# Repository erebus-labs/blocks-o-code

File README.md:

blocks-o-code
=============

#A Block of Code
+ *Title:* Physical manipulators for developing and implementing short programing routines 
+ *Project Short Name:* A Block of Code (ABC)
+ *Sponsors:* 
  + [Dr. Mike Borowczak](https://www.linkedin.com/in/mborowczak) @ [Erebus Labs](http://www.erebuslabs.com)
  + [Dr. Andrea Burrows] (http://uwyo.academia.edu/AndreaBurrows) @ [University of Wyoming] (http://www.uwyo.edu/seced/faculty-staff/andrea-burrows.html)
+ *Senior Design Team:* 
  + Jacob Mickiewicz 
  + Tyler Hart
  + Daniel Frister
  + Greg Stromire
  + Nathan Bryant
+ *PSU Academic Advisor:* [Roy Kravitz](http://www.pdx.edu/directory/name/roy_kravitz) 
+ *Targeted Users:* Infants to High School aged children, parents and their educators

##About A Block of Code

Blocks of Code are connectable “blocks” that mimic a simple-grammar programming language. 

The fundamental grammar contain 4 types of blocks:
+ Value Blocks
  + numbers (ints/doubles) – stringing these blocks together forms longer numbers [0,1,2,3,4,5]; [6,7,8,9,.]
  + variables
+ Operator Blocks
  + simple binary operators (*,/,-,+,%?): 
  + equivalence operators (<,>,==, !=,<=,>=)
+ Control Blocks (start and end)
  + if structures
  + while structures
  + explicit encapsulation ( )
+ Output Blocks

##Background

Algorithms, logical constructs and the foundations of programming are generally limited to computer-based instances. No physical manipulators exist that expose children to programming as they do for number and alphabet systems, mechanics, art, etc.  Build a prototype for building blocks that can be attached through internal magnets, these magnets perform two actions 
1. physical connection and 
2. logical circuit connections.

##Current Feature List
- [x] Open Source Hardware Design & Board (can use “closed source” components: ASICs, uC, etc.)
- [x] Must Have a Multi-Chip solution – e.g. no single SoC;
- [x] Fundamental grammar functioning; assignment; binary operators; 
- [x] Open Software Repository (github)
- [x] Multi-function blocks – e.g. 6 (or 4) binary operators on a single block; depending on connections/which side “faces up” operation changes 
- [x] Separate “power” blocks

##Wish List
- [ ] Hardware cost <$3 per unit (average cost for a set 20 = $60)
- [ ] Unexposed Connectors (e.g. Magnetic  + Inductive coupling between blocks?)
- [ ] Power: Ultra Low power operation
- [ ] Power
  - [ ] Built in power source / power pack
  - [ ] Built in power source w/inductance recharge
- [ ] Computer GUI/Phone App:
  - [ ] simulate a set of blocks (pre build) 
  - [ ] take a picture of a set of blocks and execute code (they don't even have to be REAL blocks - could be paper!)

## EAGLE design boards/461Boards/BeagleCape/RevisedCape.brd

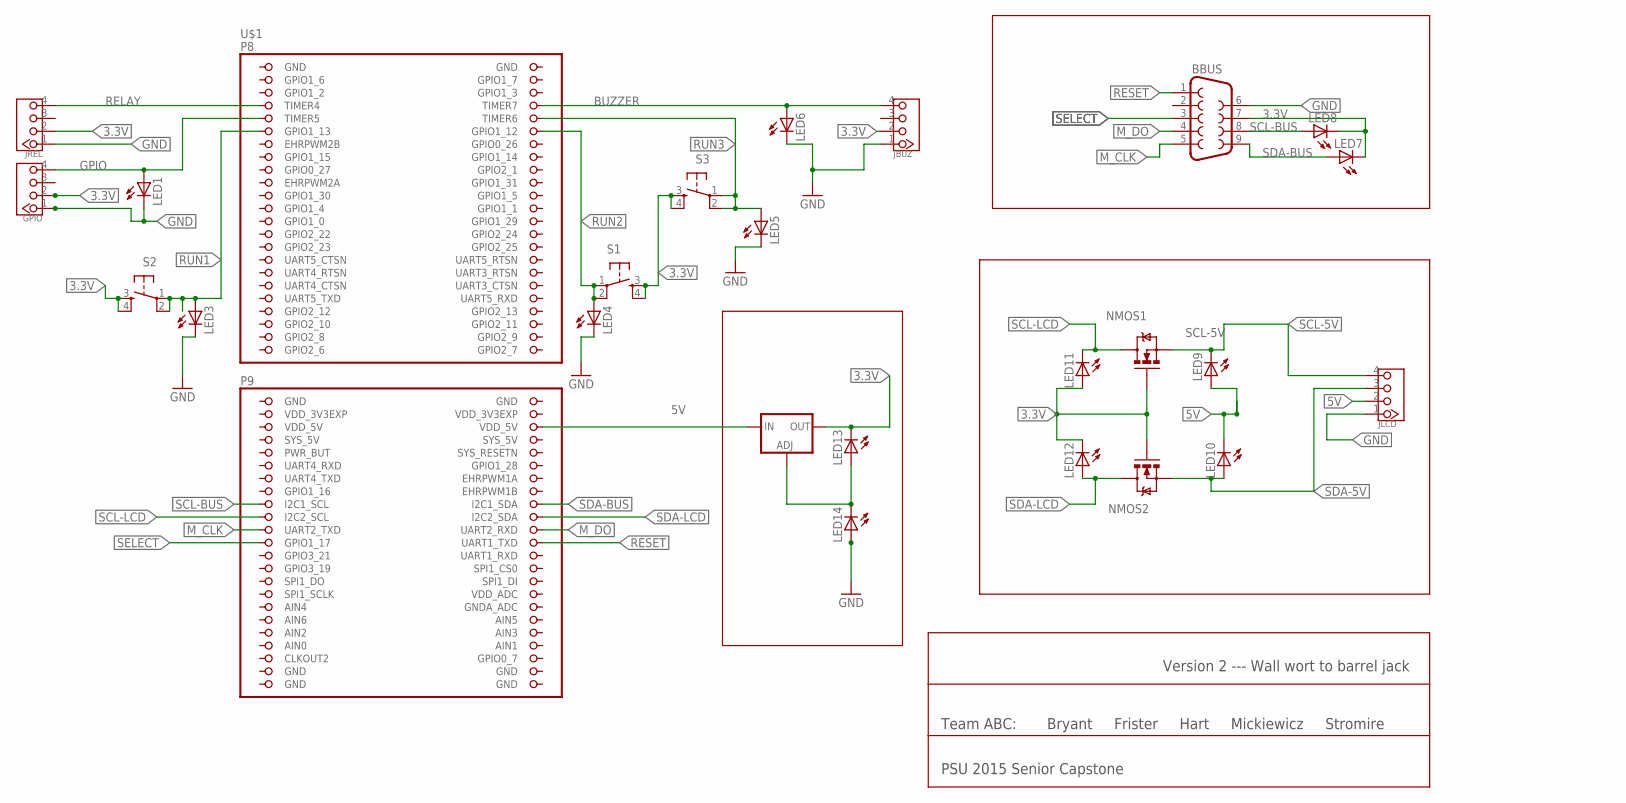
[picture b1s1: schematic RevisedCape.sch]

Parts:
3.3VREG: V_REG_317SINK; TO220-ADJ
BBUS: F09H
GPIO: TWIG-4P-2.0-2.0; 4P-2.0
JBUZ: TWIG-4P-2.0-2.0; 4P-2.0
JLCD: TWIG-4P-2.0-2.0; 4P-2.0
JREL: TWIG-4P-2.0-2.0; 4P-2.0
LED1, LED3, LED4, LED5, LED6, LED7, LED8, LED9, LED10, LED11, LED12, LED13, LED14: LED3MM
NMOS1, NMOS2: MOSFET-NCHANNEL2N7000; TO-92
S1, S2, S3: TAC_SWITCHPTH; TACTILE-PTH
U$1: BEAGLEBONE_OUTLINE; BEAGLEBONE_SHIELD

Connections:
3.3V: 3.3VREG.OUT, BBUS.7, GPIO.2, JBUZ.2, JREL.2, LED7.K (C), LED8.K (C), LED11.A, LED12.K (C), LED13.K (C), NMOS1.2 (G), NMOS2.2 (G), S1.3, S1.4, S2.3, S2.4, S3.3, S3.4
5V: 3.3VREG.IN, JLCD.2, LED9.A, LED10.K (C), U$1.52 (VDD_5V)
AIN0: U$1.85 (AIN0)
BUZZER: JBUZ.4, LED6.A, U$1.8 (TIMER7)
GND: BBUS.6, GPIO.1, JBUZ.1, JLCD.1, JREL.1, LED1.K (C), LED3.K (C), LED4.K (C), LED5.K (C), LED6.K (C), LED14.A, U$1.1 (GND), U$1.2 (GND), U$1.47 (GND), U$1.48 (GND), U$1.89 (GND), U$1.90 (GND), U$1.91 (GND), U$1.92 (GND)
GPIO: GPIO.4, LED1.A, U$1.9 (TIMER5)
M_CLK: BBUS.5, U$1.67 (UART2_TXD)
M_DO: BBUS.4, U$1.68 (UART2_RXD)
REGADJ: 3.3VREG.ADJ, LED13.A, LED14.K (C)
RELAY: JREL.4, U$1.7 (TIMER4)
RESET: BBUS.1, U$1.70 (UART1_TXD)
RUN1: LED3.A, S2.1, S2.2, U$1.11 (GPIO1_13)
RUN2: LED4.A, S1.1, S1.2, U$1.12 (GPIO1_12)
RUN3: LED5.A, S3.1, S3.2, U$1.10 (TIMER6)
SCL-5V: JLCD.4, LED9.K (C), NMOS1.1 (S)
SCL-BUS: BBUS.8, LED8.A, U$1.63 (I2C1_SCL)
SCL-LCD: LED11.K (C), NMOS1.3 (D), U$1.65 (I2C2_SCL)
SDA-5V: JLCD.3, LED10.A, NMOS2.1 (S)
SDA-BUS: BBUS.9, LED7.A, U$1.64 (I2C1_SDA)
SDA-LCD: LED12.A, NMOS2.3 (D), U$1.66 (I2C2_SDA)
SELECT: BBUS.3, U$1.69 (GPIO1_17)
SYS_5V: U$1.53 (SYS_5V)
VDD_3V3EXP: U$1.49 (VDD_3V3EXP), U$1.50 (VDD_3V3EXP)
VDD_5V: U$1.51 (VDD_5V)

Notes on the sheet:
Team ABC: Bryant Frister Hart Mickiewicz Stromire
PSU 2015 Senior Capstone
Version 2 --- Wall wort to barrel jack

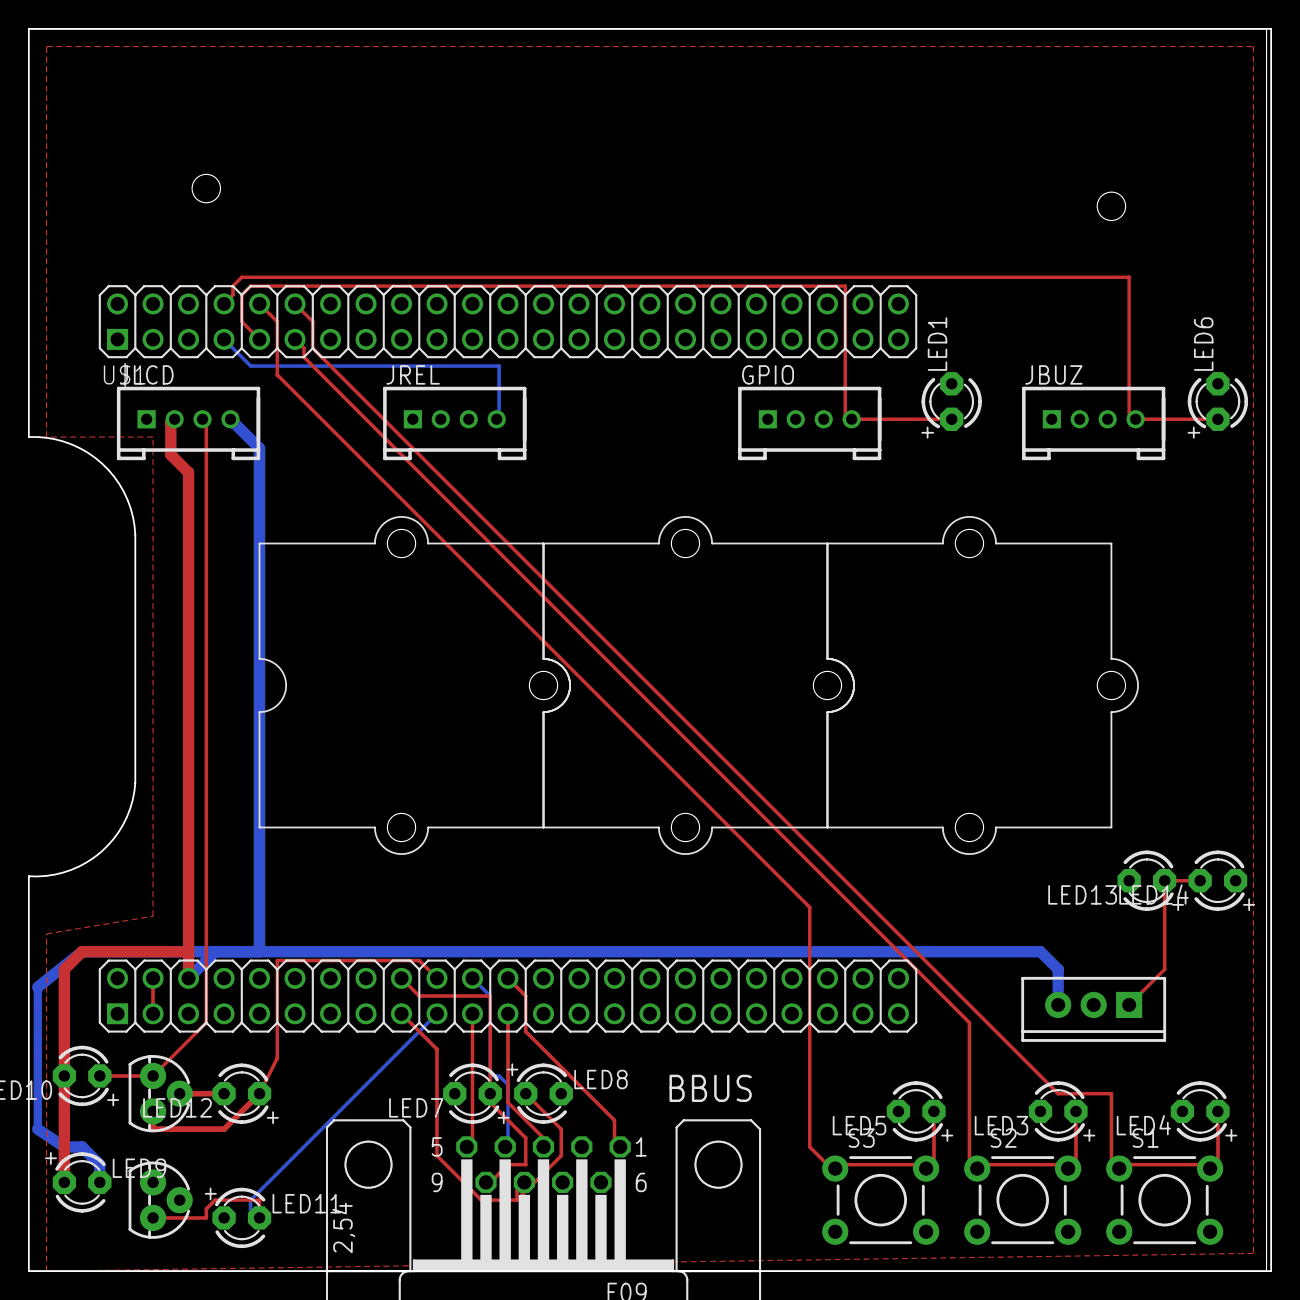
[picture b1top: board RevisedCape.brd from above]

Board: 2 copper layers, 88.9 x 88.9 mm, 28 parts (0 on the bottom side), 21 nets.

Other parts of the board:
U$2, U$3, U$4: SEEED

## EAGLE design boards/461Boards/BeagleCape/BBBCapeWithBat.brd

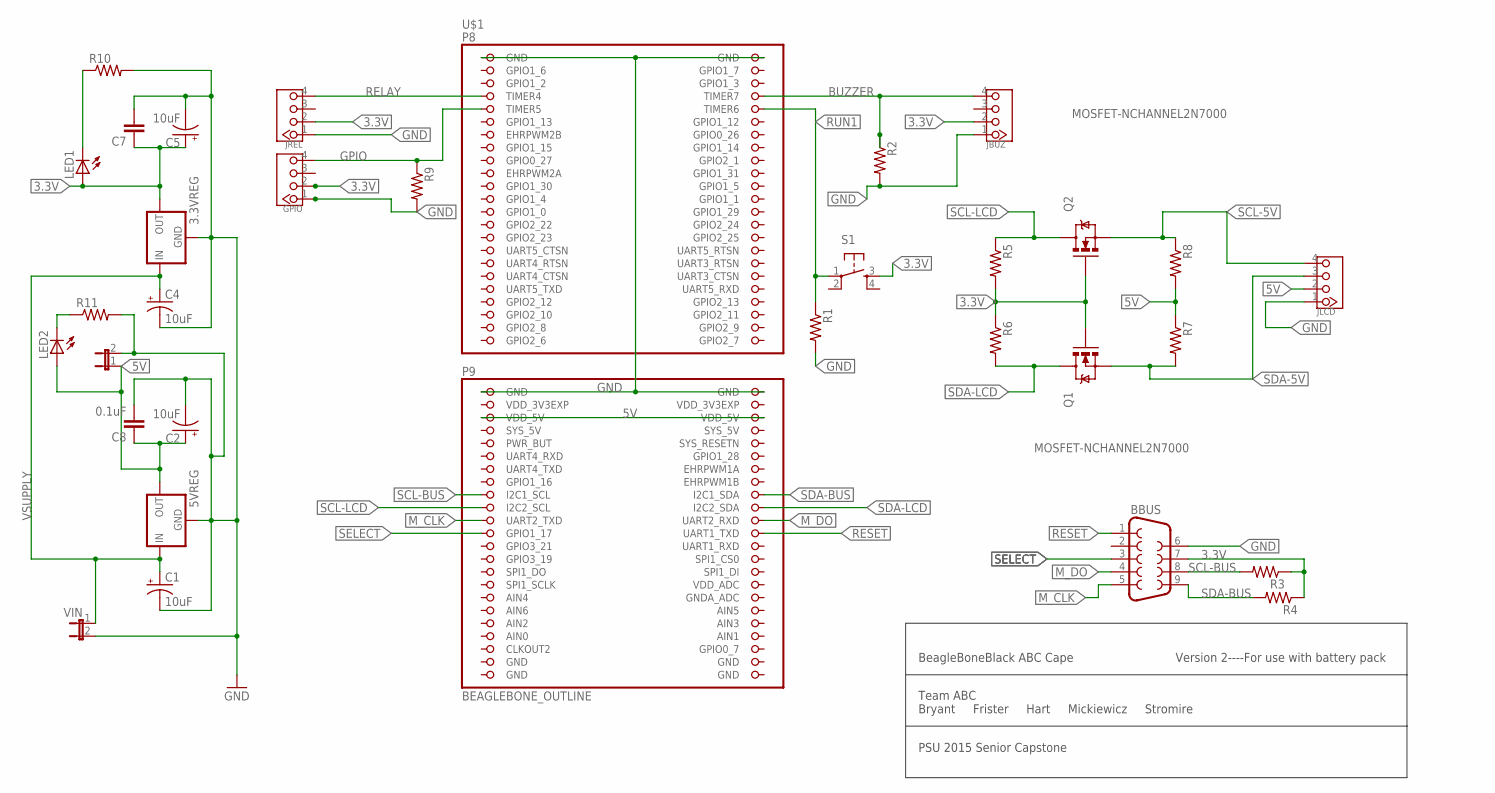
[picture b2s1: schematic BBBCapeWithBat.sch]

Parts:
3.3VREG, 5VREG: 78XXS
5VOUT: JUMPER-2PTH; 1X02
BBUS: F09H
C1, C2, C4, C5: 10uF; CPOL-RADIAL-10UF-25V
C7: CAPPTH2; CAP-PTH-SMALL2
C8: 0.1uF; CAP-PTH-SMALL2
GPIO: TWIG-4P-2.0-2.0; 4P-2.0
JBUZ: TWIG-4P-2.0-2.0; 4P-2.0
JLCD: TWIG-4P-2.0-2.0; 4P-2.0
JREL: TWIG-4P-2.0-2.0; 4P-2.0
LED1, LED2: LED3MM
Q1, Q2: MOSFET-NCHANNEL2N7000; TO-92
R1, R2, R3, R4, R5, R6, R7, R8, R9, R10, R11: R-US_0204/2V; 0204V
S1: TAC_SWITCHPTH; TACTILE-PTH
U$1: BEAGLEBONE_OUTLINE; BEAGLEBONE_SHIELD
VIN: JUMPER-2PTH; 1X02

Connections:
3.3V: 3.3VREG.OUT, BBUS.7, C5.1 (+), C7.1, GPIO.2, JBUZ.2, JREL.2, LED1.A, Q1.2 (G), Q2.2 (G), R3.1, R4.1, R5.2, R6.1, S1.3
5V: 5VOUT.1, 5VREG.OUT, C2.1 (+), C8.1, JLCD.2, LED2.A, R7.1, R8.2, U$1.51 (VDD_5V), U$1.52 (VDD_5V)
AIN0: U$1.85 (AIN0)
BUZZER: JBUZ.4, R2.1, U$1.8 (TIMER7)
GND: 3.3VREG.GND, 5VOUT.2, 5VREG.GND, BBUS.6, C1.2 (-), C2.2 (-), C4.2 (-), C5.2 (-), C7.2, C8.2, GPIO.1, JBUZ.1, JLCD.1, JREL.1, R1.2, R2.2, R9.2, R10.2, R11.2, U$1.1 (GND), U$1.2 (GND), U$1.47 (GND), U$1.48 (GND), U$1.89 (GND), U$1.90 (GND), U$1.91 (GND), U$1.92 (GND), VIN.2
GPIO: GPIO.4, R9.1, U$1.9 (TIMER5)
M_CLK: BBUS.5, U$1.67 (UART2_TXD)
M_DO: BBUS.4, U$1.68 (UART2_RXD)
unnamed: LED2.K (C), R11.1
unnamed: LED1.K (C), R10.1
RELAY: JREL.4, U$1.7 (TIMER4)
RESET: BBUS.1, U$1.70 (UART1_TXD)
RUN1: R1.1, S1.1, U$1.10 (TIMER6)
SCL-5V: JLCD.4, Q2.1 (S), R8.1
SCL-BUS: BBUS.8, R3.2, U$1.63 (I2C1_SCL)
SCL-LCD: Q2.3 (D), R5.1, U$1.65 (I2C2_SCL)
SDA-5V: JLCD.3, Q1.1 (S), R7.2
SDA-BUS: BBUS.9, R4.2, U$1.64 (I2C1_SDA)
SDA-LCD: Q1.3 (D), R6.2, U$1.66 (I2C2_SDA)
SELECT: BBUS.3, U$1.69 (GPIO1_17)
SYS_5V: U$1.53 (SYS_5V)
VDD_3V3EXP: U$1.49 (VDD_3V3EXP), U$1.50 (VDD_3V3EXP)
VSUPPLY: 3.3VREG.IN, 5VREG.IN, C1.1 (+), C4.1 (+), VIN.1

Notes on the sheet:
BeagleBoneBlack ABC Cape
Team ABC Bryant Frister Hart Mickiewicz Stromire
PSU 2015 Senior Capstone
Version 2----For use with battery pack

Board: 2 copper layers, 32 parts (0 on the bottom side), 21 nets, no tracks yet.

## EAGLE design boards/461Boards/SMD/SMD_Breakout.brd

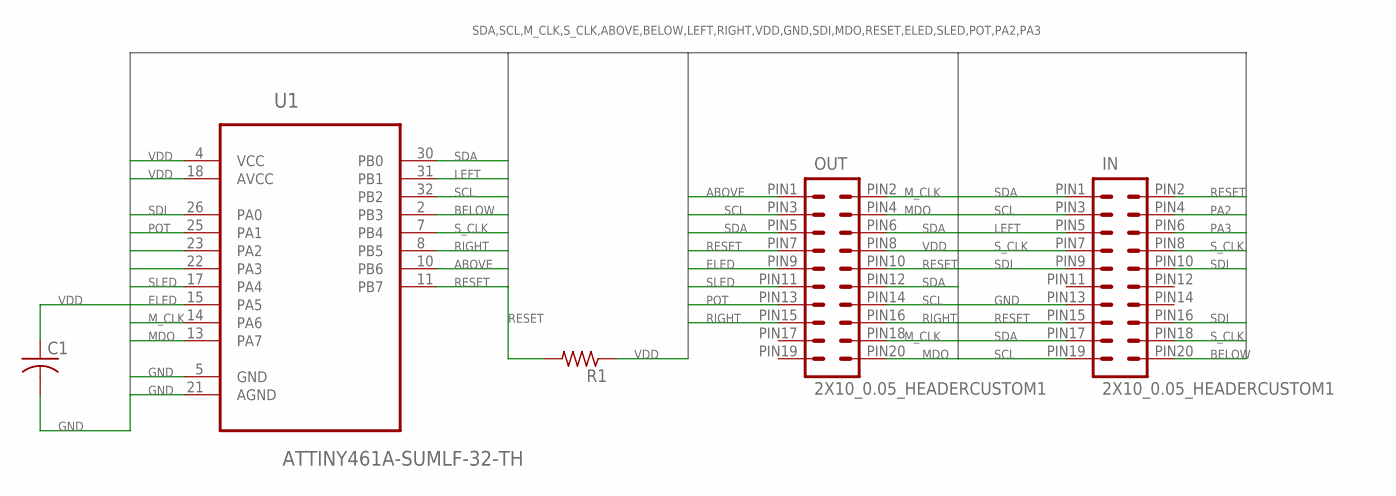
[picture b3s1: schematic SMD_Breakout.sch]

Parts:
C1: C-USC0603; C0603
IN: 2X10_0.05_HEADERCUSTOM1; 2X10_CUSTOM
OUT: 2X10_0.05_HEADERCUSTOM1; 2X10_CUSTOM
R1: R-US_R0603; R0603
U1: ATTINY461A-SUMLF-32-TH; MLF32-TH

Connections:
ABOVE: OUT.PIN1 (1), U1.10 (PB6)
BELOW: IN.PIN20 (20), U1.2 (PB3)
ELED: OUT.PIN9 (9), U1.15 (PA5)
GND: C1.2, IN.PIN13 (13), U1.5 (GND), U1.21 (AGND)
LEFT: IN.PIN5 (5), U1.31 (PB1)
MDO: OUT.PIN4 (4), OUT.PIN20 (20), U1.13 (PA7)
M_CLK: OUT.PIN2 (2), OUT.PIN18 (18), U1.14 (PA6)
PA2: IN.PIN4 (4), U1.23 (PA2)
PA3: IN.PIN6 (6), U1.22 (PA3)
POT: OUT.PIN13 (13), U1.25 (PA1)
RESET: IN.PIN2 (2), IN.PIN15 (15), OUT.PIN7 (7), OUT.PIN10 (10), R1.2, U1.11 (PB7)
RIGHT: OUT.PIN15 (15), OUT.PIN16 (16), U1.8 (PB5)
SCL: IN.PIN3 (3), IN.PIN19 (19), OUT.PIN3 (3), OUT.PIN14 (14), U1.32 (PB2)
SDA: IN.PIN1 (1), IN.PIN17 (17), OUT.PIN5 (5), OUT.PIN6 (6), OUT.PIN12 (12), U1.30 (PB0)
SDI: IN.PIN9 (9), IN.PIN10 (10), IN.PIN16 (16), U1.26 (PA0)
SLED: OUT.PIN11 (11), U1.17 (PA4)
S_CLK: IN.PIN7 (7), IN.PIN8 (8), IN.PIN18 (18), U1.7 (PB4)
VDD: C1.1, OUT.PIN8 (8), R1.1, U1.4 (VCC), U1.18 (AVCC)

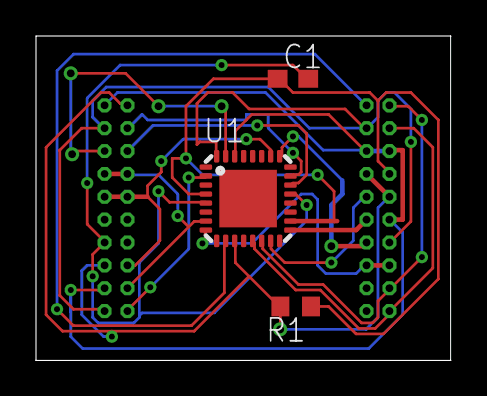
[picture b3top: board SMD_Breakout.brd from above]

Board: 2 copper layers, 23.0 x 18.0 mm, 5 parts (0 on the bottom side), 18 nets.

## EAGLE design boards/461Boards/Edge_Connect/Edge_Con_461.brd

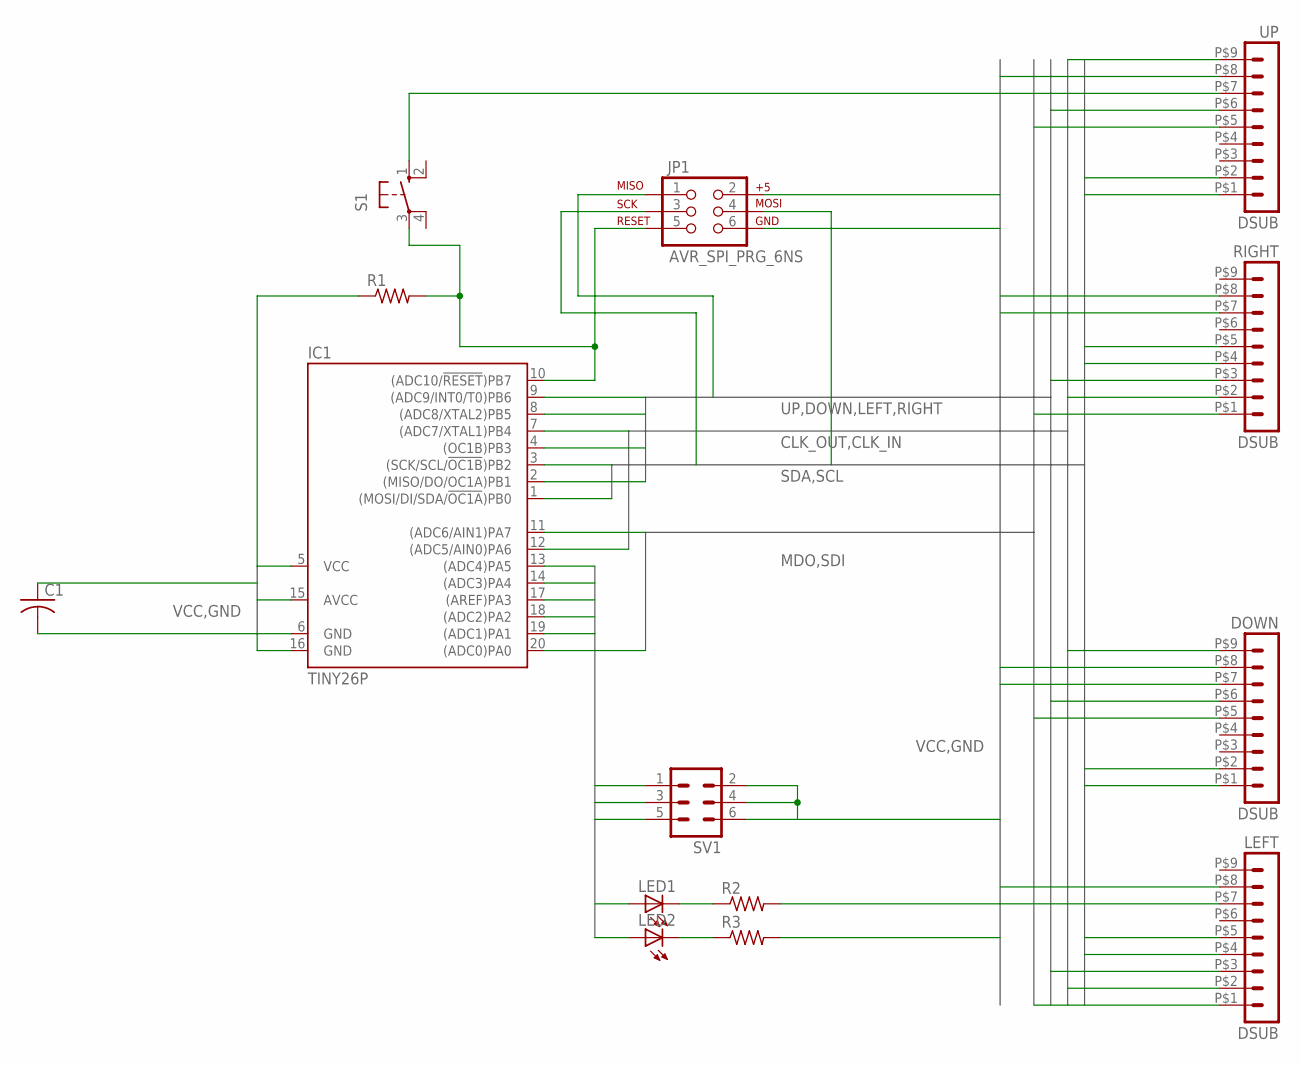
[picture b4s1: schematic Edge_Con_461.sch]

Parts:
C1: C-US025-025X050; C025-025X050
DOWN: DSUB; FOUR
IC1: TINY26P; DIL20
JP1: AVR_SPI_PRG_6NS; 2X3-NS
LED1, LED2: LED3MM
LEFT: DSUB; FOUR
R1, R2, R3: R-US_0204/5; 0204/5
RIGHT: DSUB; FOUR
S1: 10-XX; B3F-10XX
SV1: MA03-2
UP: DSUB; FOUR

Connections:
13: IC1.13 ((ADC4)PA5), LED1.A
14: IC1.14 ((ADC3)PA4), LED2.A
17: IC1.17 ((AREF)PA3), SV1.5
18: IC1.18 ((ADC2)PA2), SV1.3
19: IC1.19 ((ADC1)PA1), SV1.1
CLK_IN: DOWN.P$9 (9), IC1.7 ((ADC7/XTAL1)PB4), LEFT.P$2 (2)
CLK_OUT: IC1.12 ((ADC5/AIN0)PA6), RIGHT.P$2 (2), UP.P$9 (9)
DOWN: DOWN.P$6 (6), IC1.4 ((OC1B)PB3)
GND: C1.2, DOWN.P$7 (7), IC1.6 (GND), IC1.16 (GND), JP1.6, LEFT.P$7 (7), R2.2, R3.2, RIGHT.P$7 (7), S1.1 (S), SV1.2, SV1.4, SV1.6, UP.P$7 (7)
LEFT: IC1.2 ((MISO/DO/OC1A)PB1), JP1.1, LEFT.P$3 (3)
MDO: IC1.11 ((ADC6/AIN1)PA7), RIGHT.P$1 (1), UP.P$5 (5)
unnamed: IC1.10 ((ADC10/!RESET!)PB7), JP1.5, R1.2, S1.3
unnamed: LED1.K (C), R2.1
unnamed: LED2.K (C), R3.1
RIGHT: IC1.8 ((ADC8/XTAL2)PB5), RIGHT.P$3 (3)
SCL: DOWN.P$2 (2), IC1.3 ((SCK/SCL/!OC1B!)PB2), JP1.3, LEFT.P$5 (5), RIGHT.P$5 (5), UP.P$2 (2)
SDA: DOWN.P$1 (1), IC1.1 ((MOSI/DI/SDA/!OC1A!)PB0), JP1.4, LEFT.P$4 (4), RIGHT.P$4 (4), UP.P$1 (1)
SDI: DOWN.P$5 (5), IC1.20 ((ADC0)PA0), LEFT.P$1 (1)
UP: IC1.9 ((ADC9/INT0/T0)PB6), UP.P$6 (6)
VCC: C1.1, DOWN.P$8 (8), IC1.5 (VCC), IC1.15 (AVCC), JP1.2, LEFT.P$8 (8), R1.1, RIGHT.P$8 (8), UP.P$8 (8)

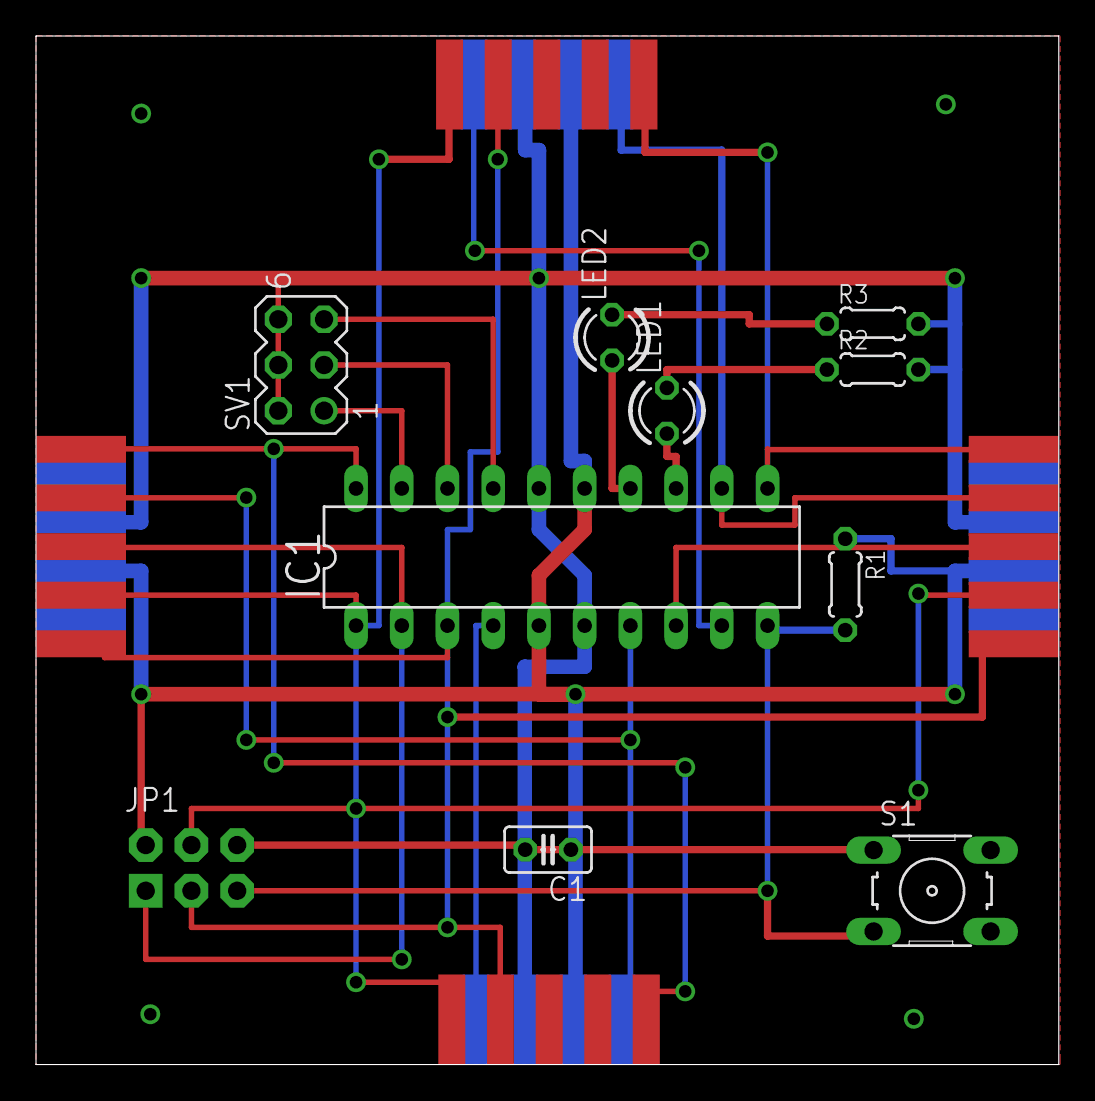
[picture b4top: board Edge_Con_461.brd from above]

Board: 2 copper layers, 56.8 x 57.1 mm, 14 parts (0 on the bottom side), 20 nets.

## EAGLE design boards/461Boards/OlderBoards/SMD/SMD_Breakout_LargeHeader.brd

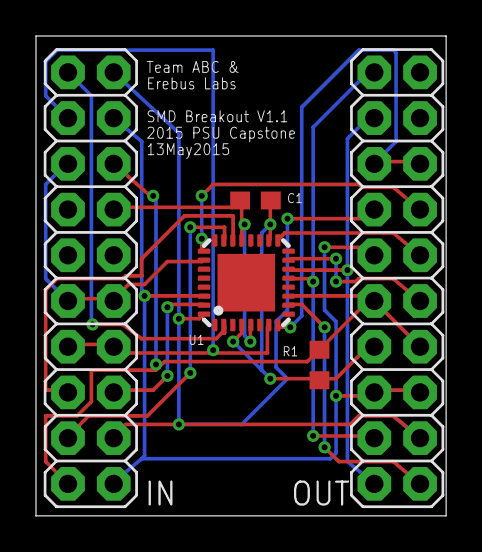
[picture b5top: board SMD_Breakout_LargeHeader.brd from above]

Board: 2 copper layers, 22.8 x 26.7 mm, 5 parts (0 on the bottom side), 18 nets.

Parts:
C1: C0603
IN: 2X10
OUT: 2X10
R1: R0603
U1: ATTINY461A-SUMLF-32-TH; MLF32-TH

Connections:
ABOVE: OUT.1, U1.10
BELOW: IN.20, U1.2
ELED: OUT.9, U1.15
GND: C1.2, IN.13, U1.5, U1.21
LEFT: IN.5, U1.31
MDO: OUT.4, OUT.20, U1.13
M_CLK: OUT.2, OUT.18, U1.14
PA2: IN.4, U1.23
PA3: IN.6, U1.22
POT: OUT.13, U1.25
RESET: IN.2, IN.15, OUT.7, OUT.10, R1.2, U1.11
RIGHT: OUT.15, OUT.16, U1.8
SCL: IN.3, IN.19, OUT.3, OUT.14, U1.32
SDA: IN.1, IN.17, OUT.5, OUT.6, OUT.12, U1.30
SDI: IN.9, IN.10, IN.16, U1.26
SLED: OUT.11, U1.17
S_CLK: IN.7, IN.8, IN.18, U1.7
VDD: C1.1, OUT.8, R1.1, U1.4, U1.18

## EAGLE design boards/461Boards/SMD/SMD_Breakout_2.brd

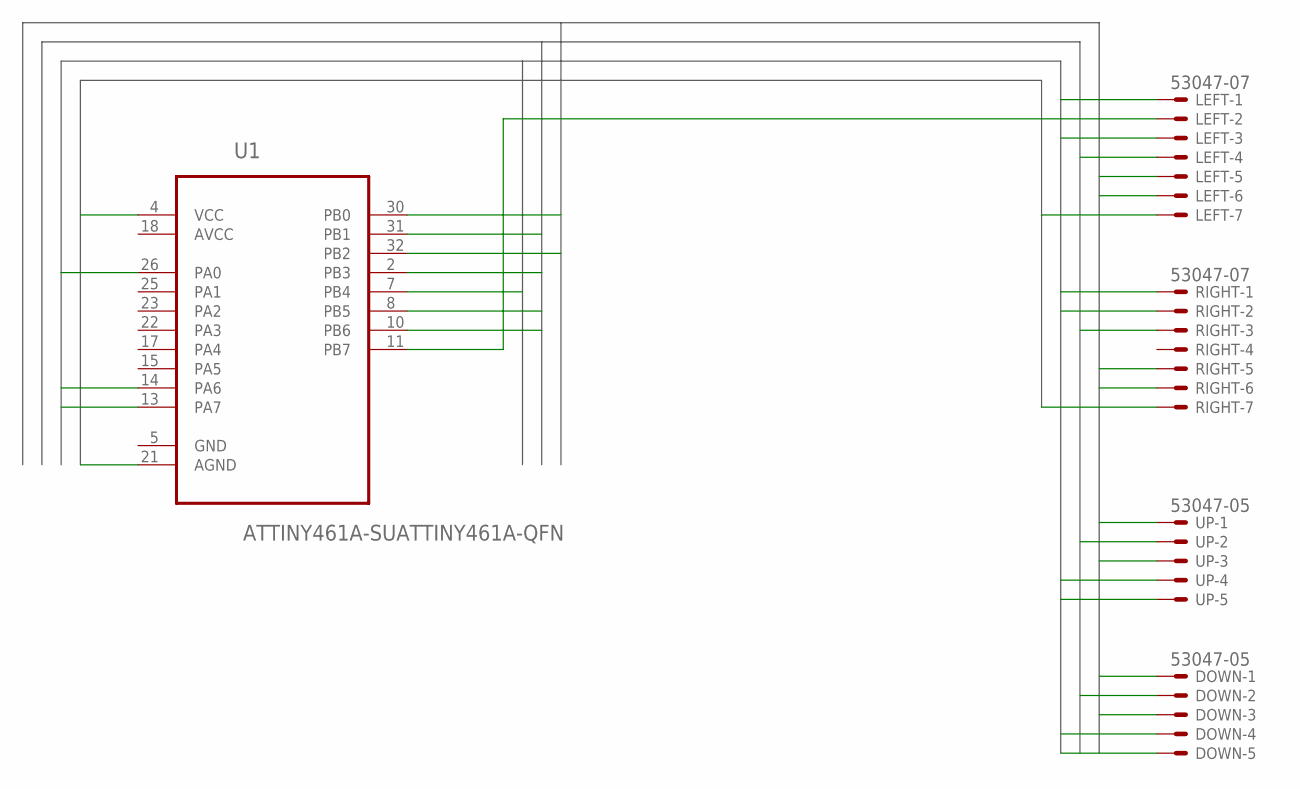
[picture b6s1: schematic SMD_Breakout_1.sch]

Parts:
DOWN: 53047-05
LEFT: 53047-07
RIGHT: 53047-07
U1: ATTINY461A-SUATTINY461A-QFN; QFN50P500X500X100-32N
UP: 53047-05

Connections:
AVCC: U1.18 (AVCC)
CLK_IN: DOWN.4, LEFT.3, U1.7 (PB4)
CLK_OUT: RIGHT.2, U1.14 (PA6), UP.4
DOWN: DOWN.2, U1.2 (PB3)
GND: RIGHT.7, U1.21 (AGND)
LEFT: LEFT.4, U1.31 (PB1)
MDO: RIGHT.1, U1.13 (PA7), UP.5
unnamed: LEFT.2, U1.11 (PB7)
RIGHT: RIGHT.3, U1.8 (PB5)
SCL: DOWN.3, LEFT.6, RIGHT.6, U1.32 (PB2), UP.3
SDA: DOWN.1, LEFT.5, RIGHT.5, U1.30 (PB0), UP.1
SDI: DOWN.5, LEFT.1, U1.26 (PA0)
UP: U1.10 (PB6), UP.2
VDD: LEFT.7, U1.4 (VCC)

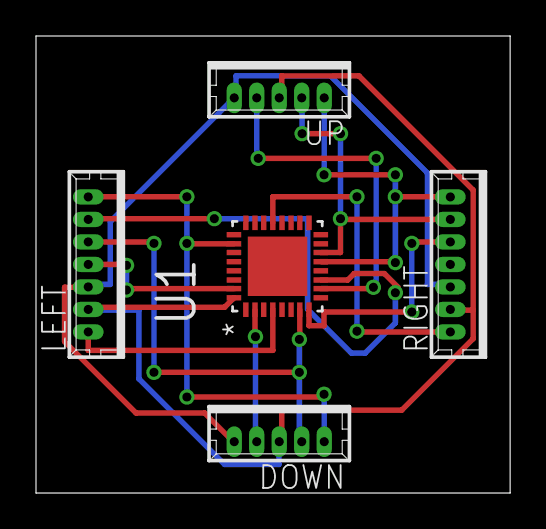
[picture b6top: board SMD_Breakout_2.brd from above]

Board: 2 copper layers, 26.3 x 25.4 mm, 5 parts (0 on the bottom side), 13 nets.

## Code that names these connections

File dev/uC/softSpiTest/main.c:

#include <stdio.h>
#include <avr/io.h>
#include <avr/interrupt.h>
#include <util/delay.h>

#define TESTING 1

#if TESTING
#define STATUS_LED	PD6
#define TOGGLE_STATUS (PORTD ^= _BV(STATUS_LED))
#endif

#define ERROR_LED	PD5
#define TOGGLE_ERROR (PORTD ^= _BV(ERROR_LED))

#ifndef PCIE0
#define PCIE0 5
#endif

#ifndef PCIE1
#define PCIE1 3
#endif

#define SPI_S_CLK	PINA1
#define SPI_S_DO	PORTA0
#define SPI_S_DI	PIND3

#define SS_F_BELOW	PINB6
#define SS_F_LEFT	PINB4


/* ATtiny2313a modifications for programming*/
#ifndef DDA1
#define DDA1 1
#endif

#ifndef DDA0
#define DDA0 0
#endif

#ifndef PCMSK1
#define PCMSK1 _SFR_IO8(0x004)
#endif

#ifndef PCINT_B_vect
#define PCINT_B_vect _VECTOR(11)
#endif

#ifndef PCINT_A_vect
#define PCINT_A_vect _VECTOR(19)
#endif

#ifndef PCINT9
#define PCINT9 1
#endif

#ifndef WDTCSR
#define WDTCSR _SFR_IO8(0x21)
#endif
/* End modifications */


// modified in ISRs
volatile static uint8_t spi_s_data_out	= 0;
volatile static uint8_t s_data_out_pos	= 8;
volatile static uint8_t spi_s_data_in	= 0;
volatile static uint8_t s_data_in_pos	= 8;
volatile static uint8_t prev_pin_b		= 0;
volatile static uint8_t prev_pin_a		= 0;
volatile static uint8_t trig_f_below	= 0;
volatile static uint8_t trig_f_left		= 0;
volatile static uint8_t tx_completed	= 0;
volatile static uint8_t i2c_addr		= 0;

volatile static uint8_t irc_counter		= 0;

static void initSoftSPI(void);
static void showAddress(void);
static void initIO(void);
static void startupSequence(void);

/**
 *  Initializes pins and registers for software SPI-slave implementation
 */
void initSoftSPI(void) {
	
	// SPI signal directions
	DDRA &= ~_BV(DDA1);				// set clock as input
	DDRD &= ~_BV(DDD3);				// set DI as input
	DDRB &= ~_BV(DDB6);				// set slave selects as inputs
	DDRB &= ~_BV(DDB4);
	DDRA |=  _BV(DDA0);				// set DO as output
	
	// SPI pull-up resistors
//	PORTA |= _BV(PORTA1);			// clock idles high (SPI CPOL = 1)
	PORTB |= _BV(PORTB6);			// slave select from below
	PORTB |= _BV(PORTB4);			// slave select from left
	
	// previous port values associated with pull-ups
//	prev_pin_a |= _BV(SPI_S_CLK);
	prev_pin_b |= _BV(SS_F_BELOW);	// initialized to high
	prev_pin_b |= _BV(SS_F_LEFT);	// "slave select" pulls low
	
	// enable pin change interrupts (PCI)
	GIMSK  |= _BV(PCIE1);			// PORTA
	GIMSK  |= _BV(PCIE0);			// PORTB
	PCMSK1 |= _BV(PCINT9);			// clk pin
	PCMSK  |= _BV(PCINT6);			// slave select from below
	PCMSK  |= _BV(PCINT4);			// slave select from left
 
	// Disable Watchdog Timer
	//	_WDR();
	// Clear WDRF in MCUSR
	MCUSR = 0x00;
	// Write one to WDCE and WDE
	WDTCSR |= (1<<WDCE) | (1<<WDE);
	// Turn off WDT
	WDTCSR = 0x00;
	
	spi_s_data_out = 6;				// initial value
	sei();							// enable interrupts
}

/**
 *  Interrupt Service Routine for Pin Change in PCIE0 (PORTB). 
	Triggered on a "slave select" pin (SS_FROM_LEFT or SS_FROM_BELOW) - 
	initiating or concluding a software SPI slave transmission.
 */
ISR(PCINT_B_vect) {
	// isolate pin changes
	uint8_t changed = PINB ^ prev_pin_b;
	
	// soft SPI slave select triggers
	if (changed & _BV(SS_F_BELOW)) {
		// trigger from below
		if (prev_pin_b & _BV(SS_F_BELOW)) {
			// transmission started, remove SS_F_LEFT interrupt, put DO MSB
			trig_f_below = 1;
			PCMSK &= ~_BV(PCINT4);
			if (s_data_out_pos) {
				PORTA = (PORTA & ~_BV(SPI_S_DO)) | ((spi_s_data_out >> --s_data_out_pos) & _BV(SPI_S_DO));
			}
		} else {
			// transmission ended
			tx_completed = 1;
		}
	} else if (changed & _BV(SS_F_LEFT)) {
		// trigger from left,
		if (prev_pin_b & _BV(SS_F_LEFT)) {
			// transmission started, remove SS_F_BELOW interrupt, put DO MSB
			trig_f_left = 1;
			PCMSK &= ~_BV(PCINT6);
			if (s_data_out_pos) {
				PORTA = (PORTA & ~_BV(SPI_S_DO)) | ((spi_s_data_out >> --s_data_out_pos) & _BV(SPI_S_DO));
			}
		} else {
			// transmission ended
			tx_completed = 1;
		}
	}

	// set i2c address if vector byte received
	if (tx_completed) {
//		TOGGLE_ERROR;

		// reset positions
		s_data_out_pos = s_data_in_pos = 8;
		
		// assign address from transmitted byte (vector)
		// position structure: bits [2:0] are x-coord, [6:3] are y-coord
		// set x-coord [2:0], increment if triggered from the left
		i2c_addr |= (spi_s_data_in & 0x07) + (trig_f_left);
		
		// set y-coord [6:3], increment if triggered from below
		i2c_addr |= (spi_s_data_in & 0x78) + (trig_f_below << 3);
		
		// disable pin change interrupts (PCI)
		GIMSK  &= ~_BV(PCIE1);			// PORTA
		GIMSK  &= ~_BV(PCIE0);			// PORTB
		PCMSK1 &= ~_BV(PCINT9);			// clk pin
		PCMSK  &= ~_BV(PCINT6);			// slave select from below
		PCMSK  &= ~_BV(PCINT4);			// slave select from left
		return;
	}
	
	// update history
	prev_pin_b = PINB;
}

/**
 *  Interrupt Service Routine for Pin Change in PCIE1 (PORTA).
	Triggered on every clock edge from incoming master-driven SPI SCK.
	Read-in bits on the DI line (and optionally write out bits on the DO).
 */
ISR(PCINT_A_vect) {
	
	// if a trigger has not happened yet, return and wait for a slave select
	if (!(trig_f_below | trig_f_left)) {
		return;
	}
	
	irc_counter++;
	if (irc_counter > 200) {
		TOGGLE_ERROR;
		irc_counter = 0;
	}
	
	// isolate pin changes
	uint8_t changed = PINA ^ prev_pin_a;
	
	// this ISR should only trigger on clock pulses
	// but checking clock pin anyway
	if (changed & _BV(SPI_S_CLK)) {
		// SPI mode 0: CPOL = 0, CPHA = 0
		if (prev_pin_a & _BV(SPI_S_CLK)) {
			// HIGH to LOW - update
			if (s_data_out_pos) {
				PORTA = (PORTA & ~_BV(SPI_S_DO)) | ((spi_s_data_out >> --s_data_out_pos) & _BV(SPI_S_DO));
			}
		} else {
			// LOW to HIGH - sample
			if (s_data_in_pos) {
				spi_s_data_in |= ((PIND & _BV(SPI_S_DI)) << --s_data_in_pos);
			}
		}
	}
	
	// update history
	prev_pin_a = PINA;
}

void showAddress(void) {
//	TOGGLE_ERROR;
	PORTB |= (i2c_addr & 0x3);
	PORTB |= ((i2c_addr & (0x3 << 3)) >> 1);
}

void initIO(void) {
	// set output pins
	DDRB |= _BV(PB0);
	DDRB |= _BV(PB1);
	DDRB |= _BV(PB2);
	DDRB |= _BV(PB3);
	DDRD |= _BV(STATUS_LED);
	DDRD |= _BV(ERROR_LED);
}

void startupSequence(void) {
	for(int i = 0; i < 4; ++i){
		_delay_ms(50);
		PORTB |= _BV(PB0 + i);
	}
	for(int i = 0; i < 4; ++i){
		_delay_ms(50);
		PORTB &= ~_BV(PB0 + i);
	}
}

int main(void) {
	initIO();
	initSoftSPI();
	
	startupSequence();
	
	while (1) {
		for(int i = 0; i < 5; ++i){
			_delay_ms(30);
		}
		
		TOGGLE_STATUS;
		
		// switch LED based on SPI input
		if (tx_completed == 1) {
			showAddress();
			tx_completed = 0;
		}
	}
	return 0; // never reached
}

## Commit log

2014-04-23 Add non-working lcd example for review
2014-04-23 Add output classes for lcd backlight control and buzzer
    Create template class for error filtering
2014-11-11 Creating and polluting README.md
    For now - just a replication of the initial proposal document.
2014-11-11 Minor edits to README.md
2014-11-12 Extra comments; layout fix
2014-11-12 Adding details on assignment operator confusion
2014-11-23 Create gh-pages branch via GitHub
2014-12-29 Initial implementation of emulator
    Implemented:
    * Expressions
    * Operators
    * Variables
    TODO:
    * Blocks
2014-12-29 Add LICENSE
2014-12-30 Initial AST Implementation
    Nodes are generated from a stack-allocated memory pool to
    minimize dynamic memory allocation keeping a direct port to
    embedded systems in mind. TODO: Make sure all parsing algorithms
    generated by bison use stack-allocation.
    Interpretation happens directly on the tree immediately after
    bison builds it.
2014-12-31 Implement blocks and control flow
    Add proper support for optional terminators (eg `;` vs. `\n`), and
    block-scope specifiers `{}`. Statement lists return the last
    expression.
    Add if and if..then statements.
    Add while, do..while and repeat loops.
2014-12-31 Add install rule to Makefile
2014-12-31 checkin out tyler's new emulator
2014-12-31 Cloning specific branches
    Adding instructions for cloning from specific git branches
2014-12-31 OSX Bison version requirements
    Adding instructions for OSX users.
2014-12-31 Adding some logical checks for OSX due to bison versioning mismatch
2014-12-31 reverting back
2015-01-01 Use fmod() instead of ()%()
    The use of the % infix operator is undefined for negative values
    of int, and the range of a double is much, much larger than the
    range of an int. fmod() works for doubles predictably and compiles
    to a single CPU instruction on many x86 architectures.
2015-01-01 Begin explicit support for <Inf> and <NaN>
2015-01-03 Greg's tests
2015-01-05 Initial Implentation of Greg's syntax
    Includes Mike's suggestions
2015-01-05 Add interactive mode
2015-01-05 Use "If What?" for ifs in interpreter mode
2015-01-05 Add 'cancel' inside blocks in interactive mode
2015-01-05 Slightly better error reporting via bison def
2015-01-12 Started proj schedule draft
2015-01-21 Template for title/ cover pages
2015-01-23 this is more local management
2015-01-23 First draft of project proposal for group revision.
2015-01-28 project proposal drafts for review before submission
2015-01-29 draft for Roy
2015-01-29 just a little clean up
2015-01-30 Updated schedule and PDFs
2015-02-02 jan1 meeting notes
2015-02-08 Add implementation to Project Proposal
    Git ignore intermediate latex files
2015-02-10 monthly schedule revision
    added a scheduled schedule revision every month
2015-02-11 Add solution pitfalls to project proposal
2015-02-11 Copy Proposal 2v3 to pdfs directory
2015-02-12 bounce back on draft
2015-02-19 Connector illustration and short write up for details discussed during 15FEB15 weekly meeting.
2015-02-19 Add central processor diagrams for docs
2015-02-20 Added uC diagram and notes to images directory resolves #47
2015-02-20 add user interface
    a simple picture and text for user interface
2015-02-20 Added uC diagram and notes to Additions directory #47
2015-02-20 compiling unified draft
2015-02-20 pdf merge
2015-02-20 prototyping uc and b3
2015-02-21 revision for @profrok
2015-02-23 Boards ready for first run
2015-02-26 submission doc for final review
2015-02-26 to pdf
2015-02-27 more proj_prop revisions
2015-02-28 mods made to PPD
2015-02-28 more mods
2015-03-02 Update to external erebus labs link
2015-03-06 Working software spi for 2313
2015-03-20 newBoards
2015-03-27 Extended daisychain code with more uC pin definitions
2015-04-01 Updated handshaking protocol.
2015-04-02 PO no 1
2015-04-02 new folder for purchase orders/ reciepts
2015-04-03 adding global code
    global code under construction
2015-04-03 latest daisychain for integration
2015-04-06 cleaning up global code
    combineduc is made by atmelstudio for 2313
2015-04-08 Updated daisychain to 461
2015-04-08 First pass for 461 layout using the drawing for edge mounting the DB9 connectors. Schematic is missing the reset push button and associated resistor (not in my current library). Extra pin header foot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
2015-04-10 combined code for 461
2015-04-10 Updated to new 461 ports
2015-04-10 Layout in progress, one footprint needs to be added to 461_Edge Connect prior to cut.
2015-04-10 code update
2015-04-10 Edge Connect Layout Complete V1.0, 3 Jumper Function Select, 2 LED spaces available, Push Button Reset.
2015-04-10 Combined BBB daisy and i2c code
2015-04-11 Moved Pull-up resistor to be pull up resistor on Edge Connect 461 board.
2015-04-16 i2c testing
2015-04-25 Pull daisy chain to separate files, implement #73 handshake
2015-04-25 Another shot at this handshake thing
2015-04-25 Updating handshake
2015-04-25 proof of concept
    uses hardcoded address and functions
2015-04-25 updated slave addressing
    #defines in main.c for i2c_address ,block function,x,y
2015-04-25 Updated HC proof for stdout
2015-04-25 Add hardcodev2
2015-04-26 Hard coded values demonstrate block and emulator functionality #76
2015-04-26 v1.1 Edge Connect Prototype Board Changes: Widened power and ground traces. Added power LED indicator. Increased all via diameters for easier plating.
2015-05-01 Can send initial vector, can't yet propagate through network.
2015-05-01 Can propagate linearly, working on 2 demensional
2015-05-03 Working daisy chain! Will clean up, confirm breadboard functionality, and integrate on proto-blocks
2015-05-03 Integrated #73 handshake with i2c framework #76, will try proto-blocks soon.
2015-05-06 SMD Breakout In progress upload.
2015-05-08 Confirmed integration on proto-blocks, closes #73. Needs function select. Potential for speed up as well.
2015-05-09 Begin output coding
    Create filter class
2015-05-13 SMD Breakout with layout complete ( all pins to the frame board with global reset). Board progress issue updated with pinouts and layout guide for design review.
2015-05-13 Uploading SMD breakout v1.1 (.1inch headers).
2015-05-15 Created data sheet directory inside documents. Added 461 datasheet and db9 through hole tech drawings. Added DB9 to programmer board.
2015-05-16 adc testing
    A guess at making the adc work
2015-05-16 New full sized boards, schematic-PDF, circuit-pdf, images for wiki etc.
2015-05-16 Raster progress - incomplete.
2015-05-17 led control
    status and error leds now are controllable on i2c #87
2015-05-17 Raster almost working, some blocks not 'announcing' themselves
2015-05-18 clean up of board
2015-05-18 Raster locationing to address #83 working and tested with the 5 proto-blocks
2015-05-20 made some more edits to board @dfrister --nice catch -- use BlockBoard folder
2015-05-20 Create lcd backlight example code
2015-05-20 50 Run Order information and BOM
2015-05-22 Trying to speed up daisychain
2015-05-22 Moderate speedup, working with 4 proto-blocks
2015-05-22 Updated programmer board to match BB2 Pinouts.
2015-05-22 Created Test Plan folder with basic connectivity test plans inside.
2015-05-22 work for the wheel
    periodic ADC reads getting returned in the combined byte
2015-05-23 Modularized daisychain, i2c, and adc code and integrated. Confirmed working on 4 proto-blocks
2015-05-24 Added Hardware 3 (programmer board), and modified wording and spacing on hardware 1 and 2. Exported each to pdf for ease of reading.
2015-05-24 Removed duplicate gerber files from Old boards (BB v2.1 files). Fixed spelling on directory.
2015-05-24 Consolidated BlockBoard and Blockboard2 into a single file. Currently .sch and .pcb files are v2.1 and gerber files are v2.2. Awaiting push to update .sch and .pcb to v.2.2.
2015-05-24 blockboard repo matching
2015-05-24 Add run_once orchestration
2015-05-26 Synchronize outputs via interpreter waiting
2015-05-26 Reorganize directory structure for merge
2015-05-26 Orchestration success! Separated lexer from global and local bus code (closes #83), integrated with parser and interpreter for confirmed LCD outputs #84.
2015-05-29 Adding test plan template and software tests 1/2 drafts.
2015-05-29 testing wheel
    modified BBB code to observe a single block's adc value
2015-05-31 Remove true interactive mode for pipe mode
2015-05-31 Separate lexer and buses. Run-once implemented. More test scripts.
2015-05-31 Create controller side install Makefile
2015-05-31 Add daemon mode to orchestration script
2015-05-31 Create systemd unit for orchestration daemon
2015-05-31 cape is running alternates included and comming
2015-05-31 a selector wheel
    0-F on a wheel, t_adc_range.py returns the listed values
2015-05-31 Updated adc test
2015-05-31 61mm Inside diameter drawing for BB2 blocks. Has 1mm offset in connector location to account for difference in male/female total length. Tested with 1 cut so far, block matches hardware. Top panel ha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
2015-06-01 all wheels draft
    four category wheels to match to abc_lexer.py
2015-06-02 Pulled code out of ISRs, started timer work.
2015-06-02 Chain with 8 blocks, but one at a time?
2015-06-03 Seems to be working except for adjacency, should be quick fix (why did I just jinx it...)
2015-06-03 Create classes for run/display buttons
2015-06-03 Add btnmanager to orchestration script
2015-06-03 Add linechange control codes to output
2015-06-03 Confirmed working on 16 boards, added i2c bounds checking. #88 #100
2015-06-03 Update of enclosure drawing after adding LED holes and adjustments to pot mounting spacing.
2015-06-05 correcting mistakes on wheel
    fixed rotation of minus and divide on operator wheel
2015-06-05 Working version of demo code, flashing 1st run.
2015-06-05 Spaced categories (closes #88), blocks flashed (closes #101), whitespace squished (closes #102)
2015-06-05 Working lexer for demo, needs tests...
2015-06-05 New lexer
2015-06-06 fixed cape design, no vias on two layer, no mod wires needed
2015-06-09 report 70% converted
2015-06-10 report formatted--Not Final Edited/ Reviewwd-- Added test plans
2015-06-10 assisted edits
2015-06-24 Adding the how to worksheet developed and used by the team for the capstone presentation.
2015-06-24 Updated README
    Modified future tense to present. Still needs work - especially in the addition of pictures / content. Then we'll repush this out the public facing page.

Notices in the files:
parts and their libraries:
SparkFun-Passives: Licensing: CC v3.0 Share-Alike You are welcome to use this library for commercial purposes.
SparkFun-DiscreteSemi: Licensing: Creative Commons ShareAlike 4.0 International - https://creativecommons.org/licenses/by-sa/4.0
